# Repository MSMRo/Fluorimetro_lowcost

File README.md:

# Fluorímetro Low Cost

Proyecto de desarrollo de un fluorímetro de bajo costo basado en Arduino. Este proyecto integra circuitos de transmisión, recepción y diseño 3D para crear un sistema completo de medición de fluorescencia.

## 📋 Descripción General

Un fluorímetro es un instrumento que mide la fluorescencia de sustancias. Este proyecto implementa una solución accesible utilizando:
- **Plataforma de control**: Arduino Mega
- **Sensor espectral**: AS7341 (multiespectrométrico)
- **Excitación**: LED controlado con DAC Delta-Sigma
- **Visualización**: Pantalla OLED Nokia 5110

## 📁 Estructura del Proyecto

```
Fluorimetro_lowcost/
├── 1_Circuito/              # Diseños de circuitos
│   ├── 1_Transmisor/        # Circuito transmisor (LED de excitación)
│   │   └── 1_TESTS/         # Pruebas y códigos
│   │       ├── 1_CORRIENTE_DELTA_SIGMA/  # Pruebas DAC Delta-Sigma
│   │       ├── 2_DAC_LED_UNO_R4/         # Pruebas para UNO R4
│   │       └── 3_TEST_KICAD/             # Diseño del shield en KiCAD
│   └── 2_Receptor/          # Circuito receptor (sensor AS7341)
│       └── 1_TEST_AS7341/   # Códigos y pruebas del sensor
├── 3_Diseño3D/              # Modelos 3D (FreeCAD)
│   ├── 1_CASE_MEGA/         # Case para Arduino Mega v1
│   └── 2_CASE_MEGA_CUBO/    # Case con cubo integrado v2
└── README.md
```

## 🔧 Circuitos

### 1. Transmisor (1_Circuito/1_Transmisor/)

Responsable de generar la luz de excitación para estimular la fluorescencia de la muestra.

**Características principales:**
- Controlador de LED con DAC Delta-Sigma para modulación de intensidad
- Múltiples versiones testeadas:
  - **Delta-Sigma para Arduino Mega**: Conversión analógica de alta resolución
  - **DAC LED UNO R4**: Variante para Arduino UNO R4
  - **Shield KiCAD**: Diseño de PCB personalizado con biblioteca 3D

**Pruebas incluidas:**
- `dac_delta_sigma_MEGA_R3_v1.ino`: Firmware para Mega
- `dac_delta_sigma_UNO_R3_v1.ino`: Firmware para UNO
- Simulaciones en SPICE para validación

### 2. Receptor (1_Circuito/2_Receptor/)

Captura el espectro de luz emitido por la muestra fluorescente.

**Sensor AS7341 (ams OSRAM):**
- **10 canales de medición**:
  - 8 canales visibles (F1-F8): 415 nm a 680 nm
  - 1 canal NIR (infrarrojo cercano): 910 nm
  - 1 canal Clear (luz blanca sin filtro)
- **Comunicación**: I2C (SDA/SCL)
- **Características**:
  - Conversores ADC independientes para cada canal
  - Ganancia ajustable (hasta 512x+)
  - Tiempo de integración configurable
  - Ideal para detectar señales tenues sin saturación

**Códigos de prueba:**
- `firmware2.ino`: Firmware principal funcional (control de LED + lectura de máximos)
- `long_onda_oled.ino`: Visualización en pantalla OLED Nokia
- `maximo_4long_onda.ino`: Muestra los 4 canales con máxima intensidad
- Librería: **Adafruit AS7341** (IDE Arduino)

**Visualización:**
- Pantalla OLED Nokia 5110 con comunicación SPI
- Display de 84x48 píxeles con limitación visual (se muestran 4 máximos canales)

## 🎨 Diseño 3D

Modelos CAD para encapsulamiento y estructura mecánica del dispositivo.

### CASE_MEGA (1_CASE_MEGA/)
- **Prototipo v1** del case para Arduino Mega
- Adaptación de diseño de terceros para incluir compartimento de cuveta
- Software: FreeCAD v1.1.1
- Basado en: [Arduino Mega 2560 Case](https://www.printables.com/model/523194-arduino-mega-2560-case/files)

### CASE_MEGA_CUBO (2_CASE_MEGA_CUBO/)
- **Prototipo v2** con integración del cubo de excitación
- Combina case del Arduino Mega + estructura para fluoróforo
- Diseño consolidado en un solo componente

## 🛠️ Herramientas y Tecnologías

| Componente | Herramienta/Tecnología |
|-----------|----------------------|
| Placa de control | Arduino Mega 2560 |
| Sensor | AS7341 (ams OSRAM) |
| Prototipado electrónico | KiCAD |
| Modelado 3D | FreeCAD v1.1.1 |
| Simulación de circuitos | SPICE |
| Programación | Arduino IDE, C/C++ |

## 📚 Bibliotecas Requeridas

- **Adafruit AS7341**: Control del sensor espectral
- **Adafruit GFX**: Gráficos para pantallas
- **Adafruit PCD8544**: Control de pantalla Nokia 5110
- **Wire**: Protocolo I2C
- **SPI**: Protocolo SPI

## 🚀 Estado del Proyecto

- ✅ Sensor AS7341 funcionando correctamente
- ✅ Control de LED con DAC Delta-Sigma
- ✅ Visualización en OLED Nokia
- ✅ Diseños 3D de prototipos
- 🔄 Optimización y validación del sistema completo

## 📝 Notas

- El firmware2 es la versión principal estable
- Se han testeado múltiples configuraciones de hardware
- Los diseños 3D están listos para impresión 3D
- Documentación con imágenes disponible en cada subdirectorio

---

*Proyecto en desarrollo - Low Cost Fluorimeter*

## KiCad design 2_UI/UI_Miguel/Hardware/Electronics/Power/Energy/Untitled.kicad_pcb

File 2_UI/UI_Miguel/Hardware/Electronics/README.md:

# Electrónica

| Módulo | Función | Estado |
| --- | --- | --- |
| [`Excitation/`](Excitation/) | Etapa de excitación y montaje de LED | V5 es la iteración más reciente |
| [`Power/Energy/`](Power/Energy/) | Conversión y distribución de alimentación | Ruta final de FlatCAM conservada |
| [`Detection/Detector/`](Detection/Detector/) | Diseño de una etapa detectora | Archivada, no usada con el detector AST actual |

Los archivos KiCad conservan nombres internos como `Untitled` y `Excite_V1`. No se renombraron porque el nombre del archivo no basta para reconstruir todas sus referencias internas.

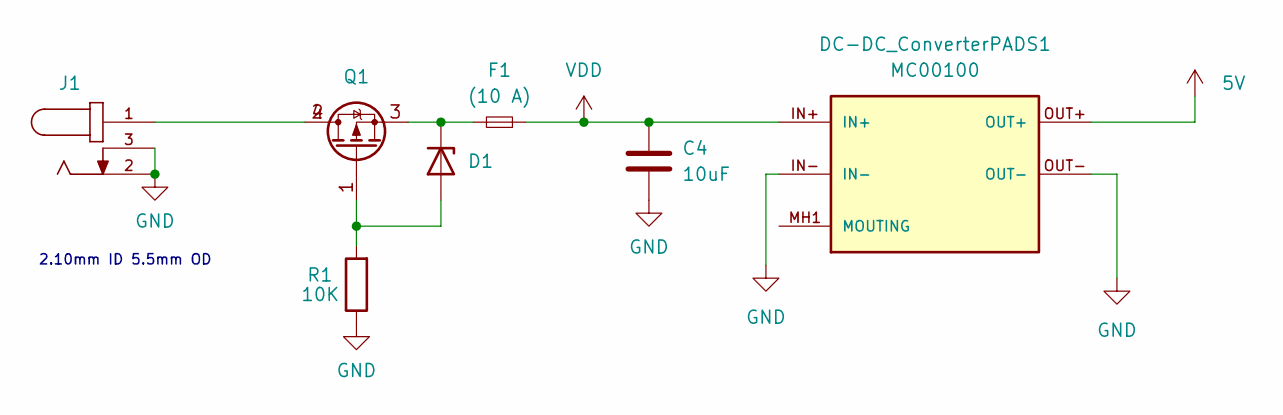
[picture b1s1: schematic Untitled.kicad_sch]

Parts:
C4: 10uF; C_0805_2012Metric
D1: D_Zener; MMSZ4700T1G
DC-DC_ConverterPADS1: MC00100; CONV_MC00100; PARTREV NA
F1: (10 A); 0154010.DRL; Part 0154010.DRL
J1: PJ-002A
Q1: DMP6023LE-13
R1: 10K; R_0805_2012Metric

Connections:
5V: DC-DC_ConverterPADS1.OUT+
GND: C4.2, DC-DC_ConverterPADS1.IN-, DC-DC_ConverterPADS1.OUT-, J1.2, J1.3, R1.1
unnamed: D1.2 (A), Q1.1, R1.2
unnamed: D1.1 (K), F1.2, Q1.3
unnamed: DC-DC_ConverterPADS1.MH1 (MOUTING), DC-DC_ConverterPADS1.MH2 (MOUTING)
unnamed: J1.1, Q1.2, Q1.4
VDD: C4.1, DC-DC_ConverterPADS1.IN+, F1.1

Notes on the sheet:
2.10mm ID 5.5mm OD

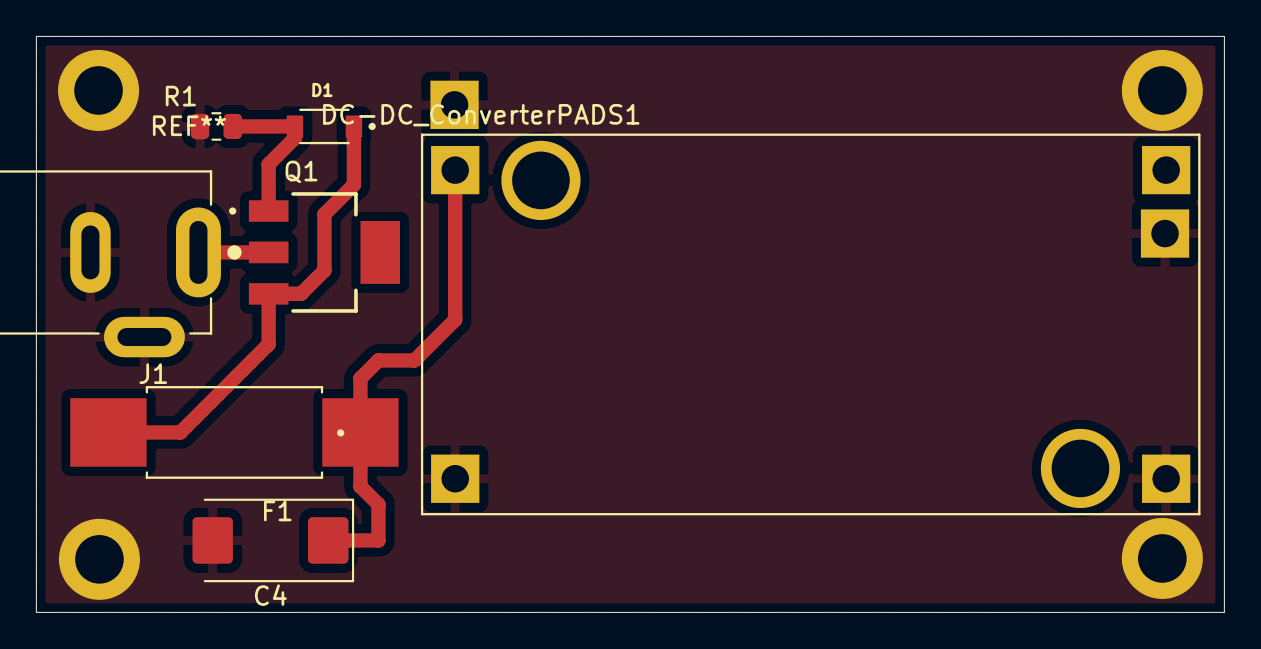
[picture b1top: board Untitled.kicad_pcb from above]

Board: 2 copper layers, 66.0 x 32.0 mm, 7 parts (0 on the bottom side), 6 nets.

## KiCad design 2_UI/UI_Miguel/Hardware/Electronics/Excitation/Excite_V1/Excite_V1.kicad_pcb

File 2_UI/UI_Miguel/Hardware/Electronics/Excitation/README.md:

# PCB Excite

El módulo Excite contiene la etapa de excitación para LED. El proyecto KiCad visible incluye un regulador MIC29150-12WU-TR, un transistor BD681, resistencias, capacitores, una entrada de habilitación y una huella de LED COB. Estos datos describen el esquema archivado, no una validación eléctrica del montaje.

## Fuente de diseño

[`Excite_V1/`](Excite_V1/) contiene el esquema, la PCB, el STEP y los respaldos del proyecto KiCad. El nombre `Excite_V1` se mantuvo a lo largo de varias iteraciones de fabricación.

## Progresión de fabricación

| Versión | Carpeta | Contenido distintivo |
| --- | --- | --- |
| V1 | [`flatcam_files/`](flatcam_files/) | Primer conjunto Gerber, perforado, mapas y rutas CNC |
| V2 | [`flatcam_files_v2/`](flatcam_files_v2/) | Segunda preparación de pista y taladro |
| V3 | [`flatcam_files_v3/`](flatcam_files_v3/) | Tercera preparación y modelo `Excite_V3.step` |
| V4 | [`flatcam_files_v4/`](flatcam_files_v4/) | Cuarta ruta CNC |
| V4 láser | [`flatcam_files_v4_laser/`](flatcam_files_v4_laser/) | DXF y SVG para fabricación con láser |
| V5 láser | [`flatcam_files_v5_laser/`](flatcam_files_v5_laser/) | Iteración más reciente para los LED específicos por banda |

Los cambios eléctricos entre V1 y V5 no se deducen solo a partir de los nombres de las salidas de fabricación. Antes de producir una placa, abre el proyecto KiCad y compara pistas, perforaciones y lista de materiales con la placa física.

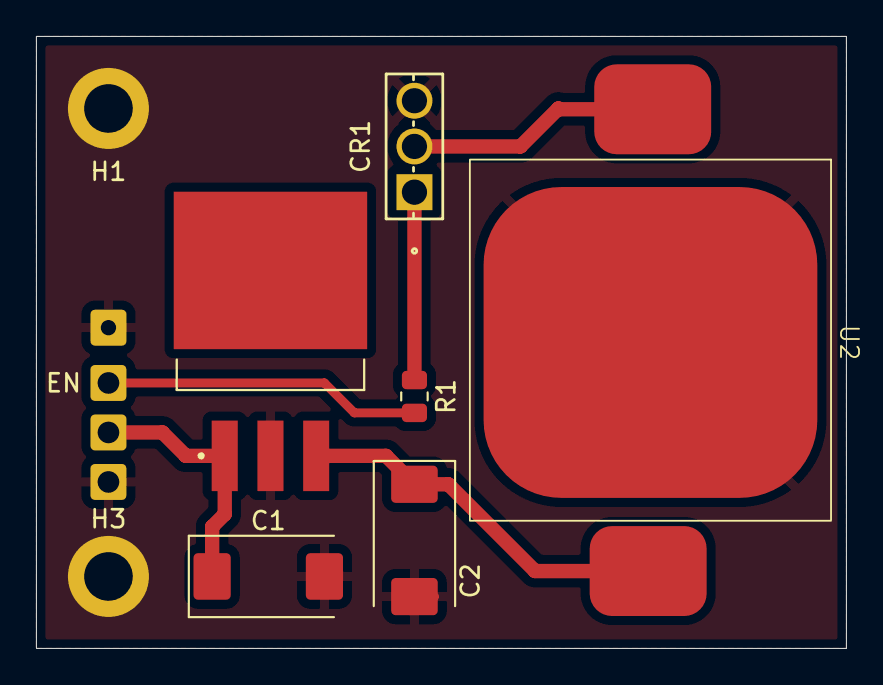
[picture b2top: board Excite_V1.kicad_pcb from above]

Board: 2 copper layers, 45.0 x 34.0 mm, 9 parts (0 on the bottom side), 6 nets.

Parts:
C1, C2: 10uF; CP_EIA-7343-15_Kemet-W
CR1: BD681
EN: Enable_from_MC; SolderWire-0.25sqmm_1x01_D0.65mm_OD2mm
H1, H3: MountingHole_2.7mm_M2.5_ISO14580_Pad
R1: 10K; R_0805_2012Metric
U1: MIC29150-12WU-TR; MIC29150-12WU
U2: 10W_COB

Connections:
GND: C1.2, C2.2, CR1.3, H1.1, H3.3, U1.2 (GND), U2.3
unnamed: CR1.1, R1.2
unnamed: CR1.2, U2.1
unnamed: EN.1, R1.1
unnamed: C2.1, U1.3 (VOUT), U2.2
VDD: C1.1, U1.1 (VIN)

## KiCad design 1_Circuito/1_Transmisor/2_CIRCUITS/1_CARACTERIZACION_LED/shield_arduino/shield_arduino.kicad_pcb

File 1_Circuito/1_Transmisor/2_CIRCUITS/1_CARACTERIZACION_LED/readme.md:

# PCB Shield de Caracterización de LED - Arduino Mega 2560

Este directorio contiene el diseño y la documentación de la placa de circuito impreso (**PCB Shield**) desarrollada en KiCAD para la caracterización y control del LED de excitación en el **Fluorímetro de Bajo Costo**.

---

## 📋 Descripción General

La shield se conecta directamente sobre un **Arduino Mega 2560 R3** y tiene como objetivo principal proporcionar una **fuente de corriente constante regulable y de alta resolución** para alimentar el LED de excitación de la muestra fluorescente.

Al no contar el Arduino Mega con un convertidor digital-analógico (DAC) interno, esta PCB implementa una topología de **DAC Delta-Sigma por Hardware (PWM de alta frecuencia + Filtro Pasa-Bajos)** junto con una etapa de control de corriente basada en un **Amplificador Operacional y Transistor NPN**.

---

## ✨ Características Principales

- **Formato Shield Arduino Mega 2560**: Ensamblado directo mediante headers apilables sin necesidad de cableado externo.
- **Generación de Voltaje Referencia (DAC Delta-Sigma)**:
  - Utiliza el **Timer 1** del ATmega2560 (Pin **D11**) en modo *Fast PWM de 10 bits* (~15.6 kHz).
  - Filtro RC de suavizado pasa-bajos integrado para obtener un voltaje analógico $V_{set}$ continuo y estable ($0\text{V} - 5\text{V}$, resolución mínima ~4.88 mV).
- **Driver de Corriente Constante para LED**:
  - Etapa analógica formada por un **Amplificador Operacional LM358** y un **Transistor BJT NPN (2N3904 / 2N2222)**.
  - Regula de forma lineal la corriente del LED en el rango aprox. de $0\text{ mA}$ a $16\text{ mA}$ (según la resistencia de detección $R_{sense}$).
- **Entrada de Ajuste Manual**:
  - Potenciómetro lineal de $10\text{ k}\Omega$ (**RV1**) conectado a la entrada analógica **A3** para ajuste dinámico o manual de intensidad.
- **Interfaz de Expansión I2C (QWIIC 5V)**:
  - Puerto **QWIIC (J4)** con líneas $5\text{V}$, $\text{GND}$, $\text{SDA}$ y $\text{SCL}$ para acoplar el sensor multiespectral **AS7341** o sensores I2C auxiliares.
- **Conexión para Pantalla Nokia 5110**:
  - Salidas de comunicación SPI (señales `CLK`, `DIN`, `DC`, `CE`, `RST`) asignadas en la placa para conectar una pantalla OLED/LCD gráfica Nokia 5110 ($84\times 48$).
- **Pulsador de Reset Local**:
  - Botón táctil **SW1** acoplado al pin `RESET` del microcontrolador.

---

## 📐 Esquema del Circuito y Principio de Funcionamiento

### Principio Físico/Electrónico
1. **DAC Delta-Sigma**: El software configura el registro `OCR1A` del Timer 1 en el Arduino Mega para emitir un ciclo de trabajo PWM proporcional a la tensión deseada. El filtro pasa-bajos convierte este tren de pulsos en un voltaje DC $V_{set}$.
2. **Lazo de Control de Corriente**: El amplificador operacional LM358 ajusta la base del transistor $Q1$ para igualar la tensión en su entrada inscripta con el voltaje de la resistencia $R_{sense}$. Así, la corriente que atraviesa el LED resulta:
   $$I_{LED} = \frac{V_{set}}{R_{sense}}$$

---

## 🛠️ Listado de Componentes Clave (BOM)

| Referencia | Componente | Descripción / Encapsulado |
| :--- | :--- | :--- |
| **U1** | **LM358** | Amplificador Operacional Doble (DIP-8 / SOIC-8) |
| **Q1** | **2N3904 / 2N2222** | Transistor NPN BJT (TO-92) |
| **D1** | **LED Excitación** | LED indicador/excitación o Bornera de conexión |
| **RV1** | **Potenciómetro 10k** | Ajuste analógico de tensión de referencia |
| **R1, R2, R5, R6, R7, R8, R9, R10** | **Resistencias** | Varias ($1\text{k}\Omega$, $10\text{k}\Omega$, etc. THT / SMD) |
| **C1** | **Capacitor $1\ \mu\text{F}$** | Capacitor de filtrado pasa-bajos |
| **SW1** | **Pulsador Tactil** | Switch de Reset |
| **J4** | **Conector QWIIC 5V** | Conector JST-SH de 4 pines para I2C |
| **Headers SPI** | **Conector 8 Pines** | Conexión para pantalla Nokia 5110 (`CLK`, `DIN`, `DC`, `CE`, `RST`) |
| **Shield Headers** | **Tiras de Pines Male/Female** | Conexión a zócalos de Arduino Mega 2560 |

---

## 📌 Asignación de Pines (Pinout Shield)

| Pin Arduino Mega | Función en la Shield | Descripción |
| :--- | :--- | :--- |
| **D11** | `PWM_DAC` | Salida de Timer 1 para DAC Delta-Sigma |
| **A3** | `POT_IN` | Lectura de voltaje del potenciómetro RV1 |
| **SDA / SCL** | `I2C` | Bus de datos I2C (Conector QWIIC J4 para AS7341) |
| **Pins SPI / GPIO** | `NOKIA_5110` | Señales `CLK`, `DIN`, `DC`, `CE`, `RST` |
| **5V / GND** | `PWR` | Alimentación general del circuito y sensores |
| **RESET** | `RST_BTN` | Pulsador de reinicio SW1 |

---

## 📂 Archivos del Proyecto KiCAD

La carpeta [`shield_arduino/`](./shield_arduino/) contiene los archivos fuente del proyecto en KiCAD:

- 📄 `shield_arduino.kicad_sch`: Esquema eléctrico completo.
- 📇 `shield_arduino.kicad_pcb`: Diseño de la placa de circuito impreso (rutas, planos de GND, capas de cobre).
- ⚙️ `shield_arduino.kicad_pro`: Archivo de proyecto de KiCAD.
- 📦 `shield_arduino-*.gbr` y `shield_arduino.drl`: Archivos **Gerber** y de taladro listos para fabricación (JLCPCB, PCBWay, etc.).
- 📐 `Librerias_step/`: Modelos 3D STEP de componentes (Pantalla Nokia 5110, Potenciómetro, etc.).

---

## 💻 Código de Prueba Rápida (Arduino Mega)

Para verificar el funcionamiento del DAC Delta-Sigma y la salida del LED, se puede cargar el siguiente firmware:

```cpp
/*
  Control de Corriente LED por DAC Delta-Sigma (10 bits)
  Plataforma: Arduino Mega 2560 (Pin D11 - Timer 1)
*/

const int pinDAC = 11; 
const int pinPot = A3;
const float vMax = 5.0;

void setup() {
  Serial.begin(115200);
  pinMode(pinDAC, OUTPUT);

  // Configuración de Timer 1 para Fast PWM de 10 bits (~15.6 kHz)
  TCCR1A = _BV(COM1A1) | _BV(WGM11) | _BV(WGM10);
  TCCR1B = _BV(WGM12)  | _BV(CS10); // Prescaler 1
}

void fijarVoltajeDAC(float voltios) {
  if (voltios < 0.0) voltios = 0.0;
  if (voltios > vMax) voltios = vMax;
  int valorPWM = (voltios * 1023.0) / vMax;
  OCR1A = valorPWM; 
}

void loop() {
  // Lectura del potenciómetro
  float vRef = analogRead(pinPot) * (vMax / 1023.0);
  fijarVoltajeDAC(vRef);
  
  Serial.print("Voltaje de referencia fijado: ");
  Serial.print(vRef);
  Serial.println(" V");
  delay(100);
}
```

---

## 🔗 Enlaces Relacionados

- 📖 [Documentación de pruebas y simulaciones Delta-Sigma](../1_TESTS/1_CORRIENTE_DELTA_SIGMA/readme.md)
- 🔬 [Receptor y Sensor Espectral AS7341](../../2_Receptor/readme.md)
- 🏠 [Volver al README Principal del Proyecto](../../../README.md)

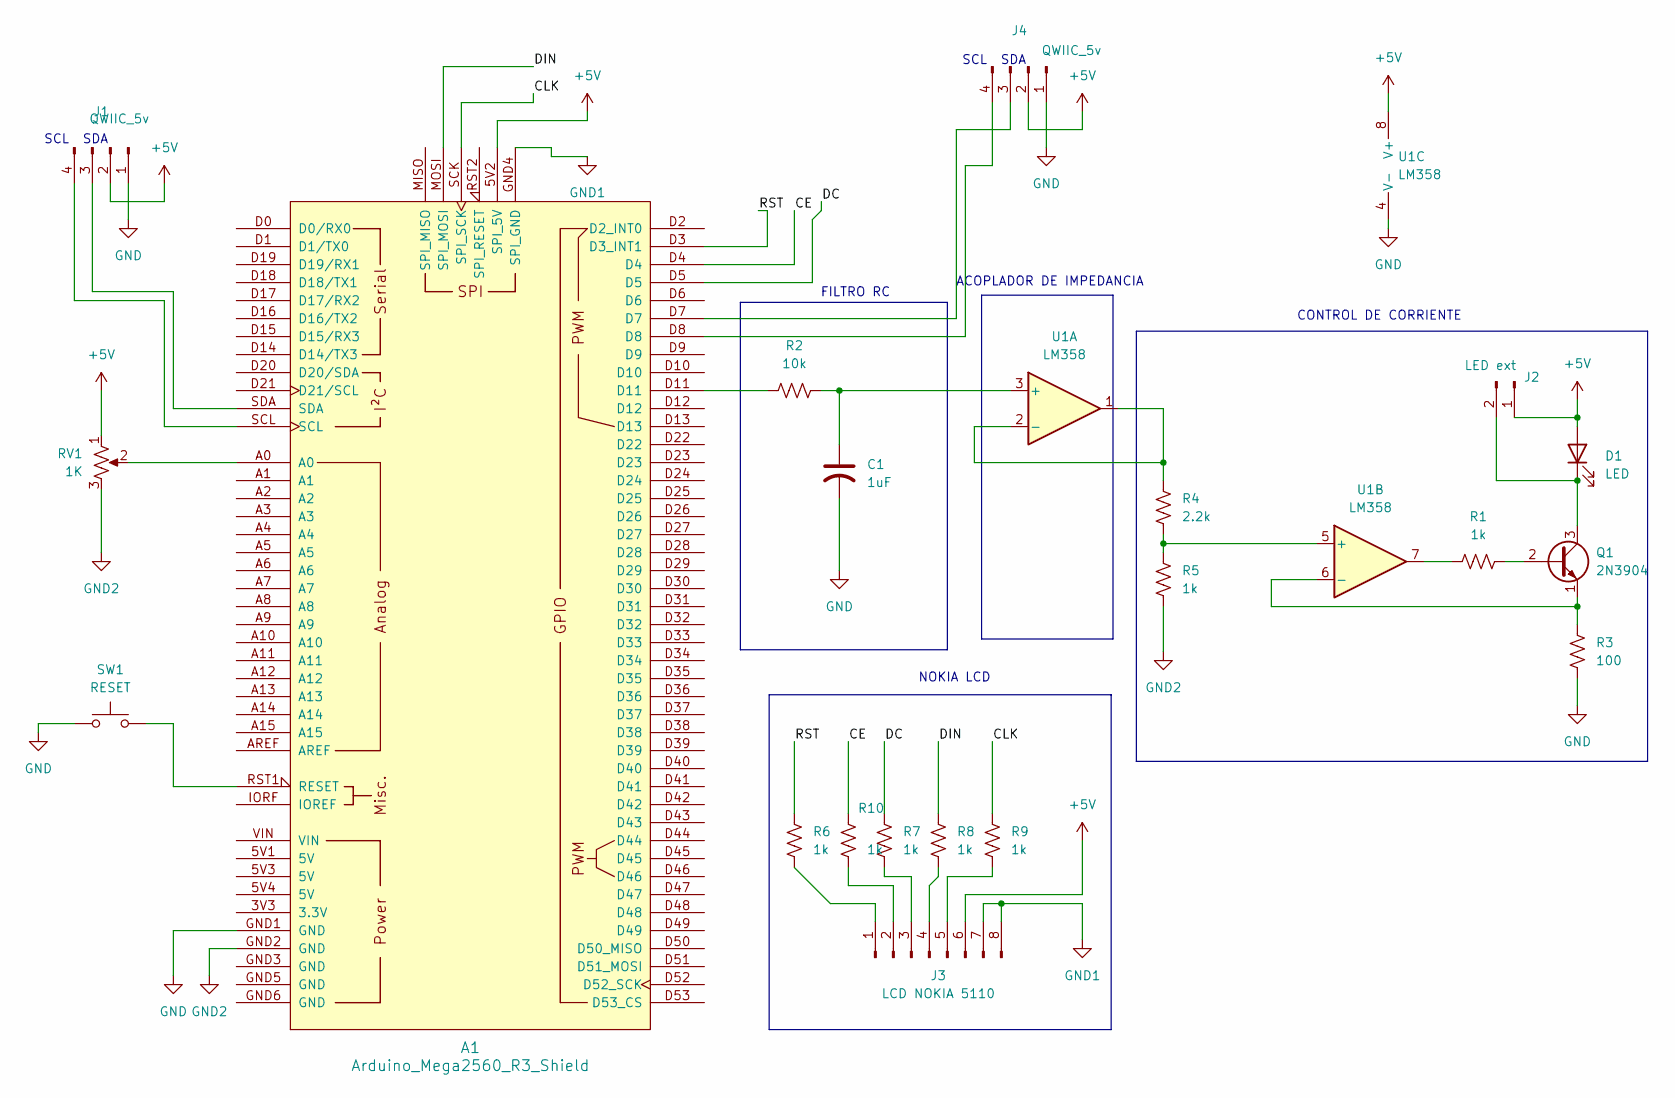
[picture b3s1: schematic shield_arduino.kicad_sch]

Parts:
A1: Arduino_Mega2560_R3_Shield
C1: 1uF; CP_Radial_D5.0mm_P2.50mm
D1: LED; LED_D3.0mm
J1, J4: QWIIC_5v; PinHeader_1x04_P2.54mm_Vertical
J2: LED ext; PinHeader_1x02_P2.54mm_Vertical
J3: LCD NOKIA 5110; PinSocket_1x08_P2.54mm_Vertical
Q1: 2N3904; TO-92_Inline
R1, R5, R6, R7, R8, R9, R10: 1k; R_Axial_DIN0207_L6.3mm_D2.5mm_P10.16mm_Horizontal
R2: 10k; R_Axial_DIN0207_L6.3mm_D2.5mm_P10.16mm_Horizontal
R3: 100; R_Axial_DIN0207_L6.3mm_D2.5mm_P10.16mm_Horizontal
R4: 2.2k; R_Axial_DIN0207_L6.3mm_D2.5mm_P10.16mm_Horizontal
RV1: 1K; Potentiometer_Alps_RK163_Single_Horizontal
SW1: RESET; SW_PUSH_6mm_H5mm
U1: LM358; DIP-8_W7.62mm

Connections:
+5V: A1.5V2 (SPI_5V), D1.2 (A), J1.2, J2.1, J3.6, J4.2, RV1.1, U1.8 (V+)
/CE: A1.D4, R10.1
/CLK: A1.SCK (SPI_SCK), R9.1
/DC: A1.D5, R7.1
/DIN: A1.MOSI (SPI_MOSI), R8.1
/RST: A1.D3 (D3_INT1), R6.1
GND: A1.GND1 (GND), C1.2, J1.1, J4.1, R3.2, SW1.1, U1.4 (V-)
GND1: A1.GND4 (SPI_GND), J3.7, J3.8
GND2: A1.GND2 (GND), R5.2, RV1.3
unnamed: A1.A0, RV1.2
unnamed: A1.D11, R2.2
unnamed: A1.RST1 (RESET), SW1.2
unnamed: D1.1 (K), J2.2, Q1.3 (C)
unnamed: A1.SDA, J1.3
unnamed: A1.SCL, J1.4
unnamed: J3.1, R6.2
unnamed: J3.2, R10.2
unnamed: J3.3, R7.2
unnamed: J3.4, R8.2
unnamed: J3.5, R9.2
unnamed: A1.D7, J4.3
unnamed: A1.D8, J4.4
unnamed: Q1.2 (B), R1.1
unnamed: Q1.1 (E), R3.1, U1.6 (-)
unnamed: R1.2, U1.7
unnamed: C1.1, R2.1, U1.3 (+)
unnamed: R4.1, U1.1, U1.2 (-)
unnamed: R4.2, R5.1, U1.5 (+)

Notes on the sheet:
SCL SDA
NOKIA LCD
FILTRO RC
ACOPLADOR DE IMPEDANCIA
CONTROL DE CORRIENTE

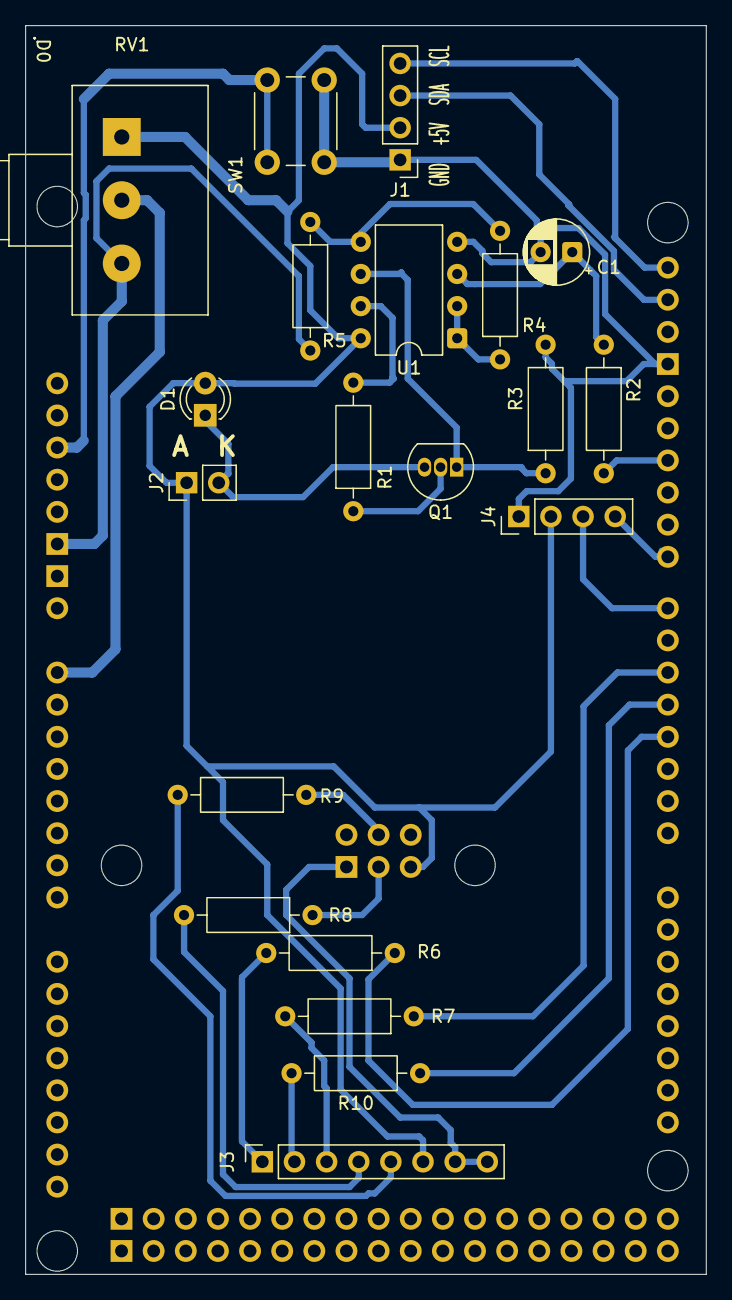
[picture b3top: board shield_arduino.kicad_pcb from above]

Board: 2 copper layers, 53.8 x 98.7 mm, 21 parts (0 on the bottom side), 28 nets.
